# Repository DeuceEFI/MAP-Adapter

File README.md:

# SSOP-8 to SOP-8 Adapter board for Jaguar 0.4-alpha to 0.7-alpha PCBs

JAG 06/16/2014 0017 EDT (GMT-0400)

### Introduction

This adapter board allows the use of the Freescale SSOP-8 (Super Small Outline Package) pressure sensors to be used for the MAP or AAP sensors on the Jaguar 0.4-alpha to 0.7-alpha PCBs.  The adapter board/sensor can be soldered on by hand or by reflow oven.

Please see forum.diyefi.org for the most up to date information and links for this project and all of the other aspects of the FreeEMS project.

### Goals

The goal of this adapter board is to allow users who want to use the smaller footprint SSOP-8 sensors with the existing Jaguar PCBs which have the SOP-8 footprint pads.

### Status

This adapter board is ready for use.

### Changes

Please send any changes that you make to the MAP-Adapter project back upstream to Andy Goss' copy at https://github.com/DeuceEFI/MAP-Adapter

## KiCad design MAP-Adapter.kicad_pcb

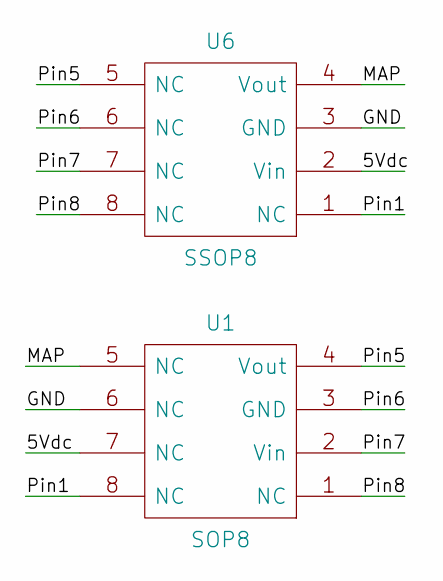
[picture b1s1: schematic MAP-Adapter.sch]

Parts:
U1: SOP8
U6: SSOP8

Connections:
/5Vdc: U1.7 (NC), U6.2 (Vin)
/GND: U1.6 (NC), U6.3 (GND)
/MAP: U1.5 (NC), U6.4 (Vout)
/Pin1: U1.8 (NC), U6.1 (NC)
/Pin5: U1.4 (Vout), U6.5 (NC)
/Pin6: U1.3 (GND), U6.6 (NC)
/Pin7: U1.2 (Vin), U6.7 (NC)
/Pin8: U1.1 (NC), U6.8 (NC)

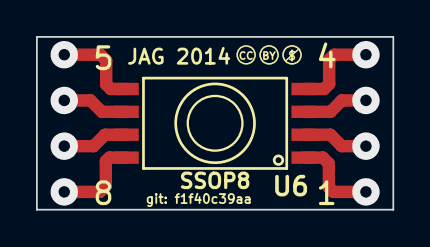
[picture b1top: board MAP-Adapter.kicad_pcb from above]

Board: 2 copper layers, 19.8 x 9.6 mm, 3 parts (1 on the bottom side), 8 nets.

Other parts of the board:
CC-logo: G**; CC-BY-NC-logo

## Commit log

2014-06-16 Moved the alternate design to the main directory.
2014-06-16 Updated README.md with the current status of the adapter board.
2014-06-16 Added git hash to KiCAD files and created the Gerber files.
